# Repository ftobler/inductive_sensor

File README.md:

# inductive sensor with STM32

This is a open source inductive sensor using a STM32G030K8T6 MCU.

---

PCB has been made with Eagle, Software with STM32CubeIDE.

The sensor is capable of sub mm accuracy. There might be linearity errors.

The TX coil is driven with 125kHz. A new measurement can be made every 50ms. The speed is limited mainly due to lack of processing power and FPU. During one measurement, the TX coil is ON for 2.8ms. During the short ON time, data is gathered which is later processed. The amount which can be gathered is limited by RAM available.

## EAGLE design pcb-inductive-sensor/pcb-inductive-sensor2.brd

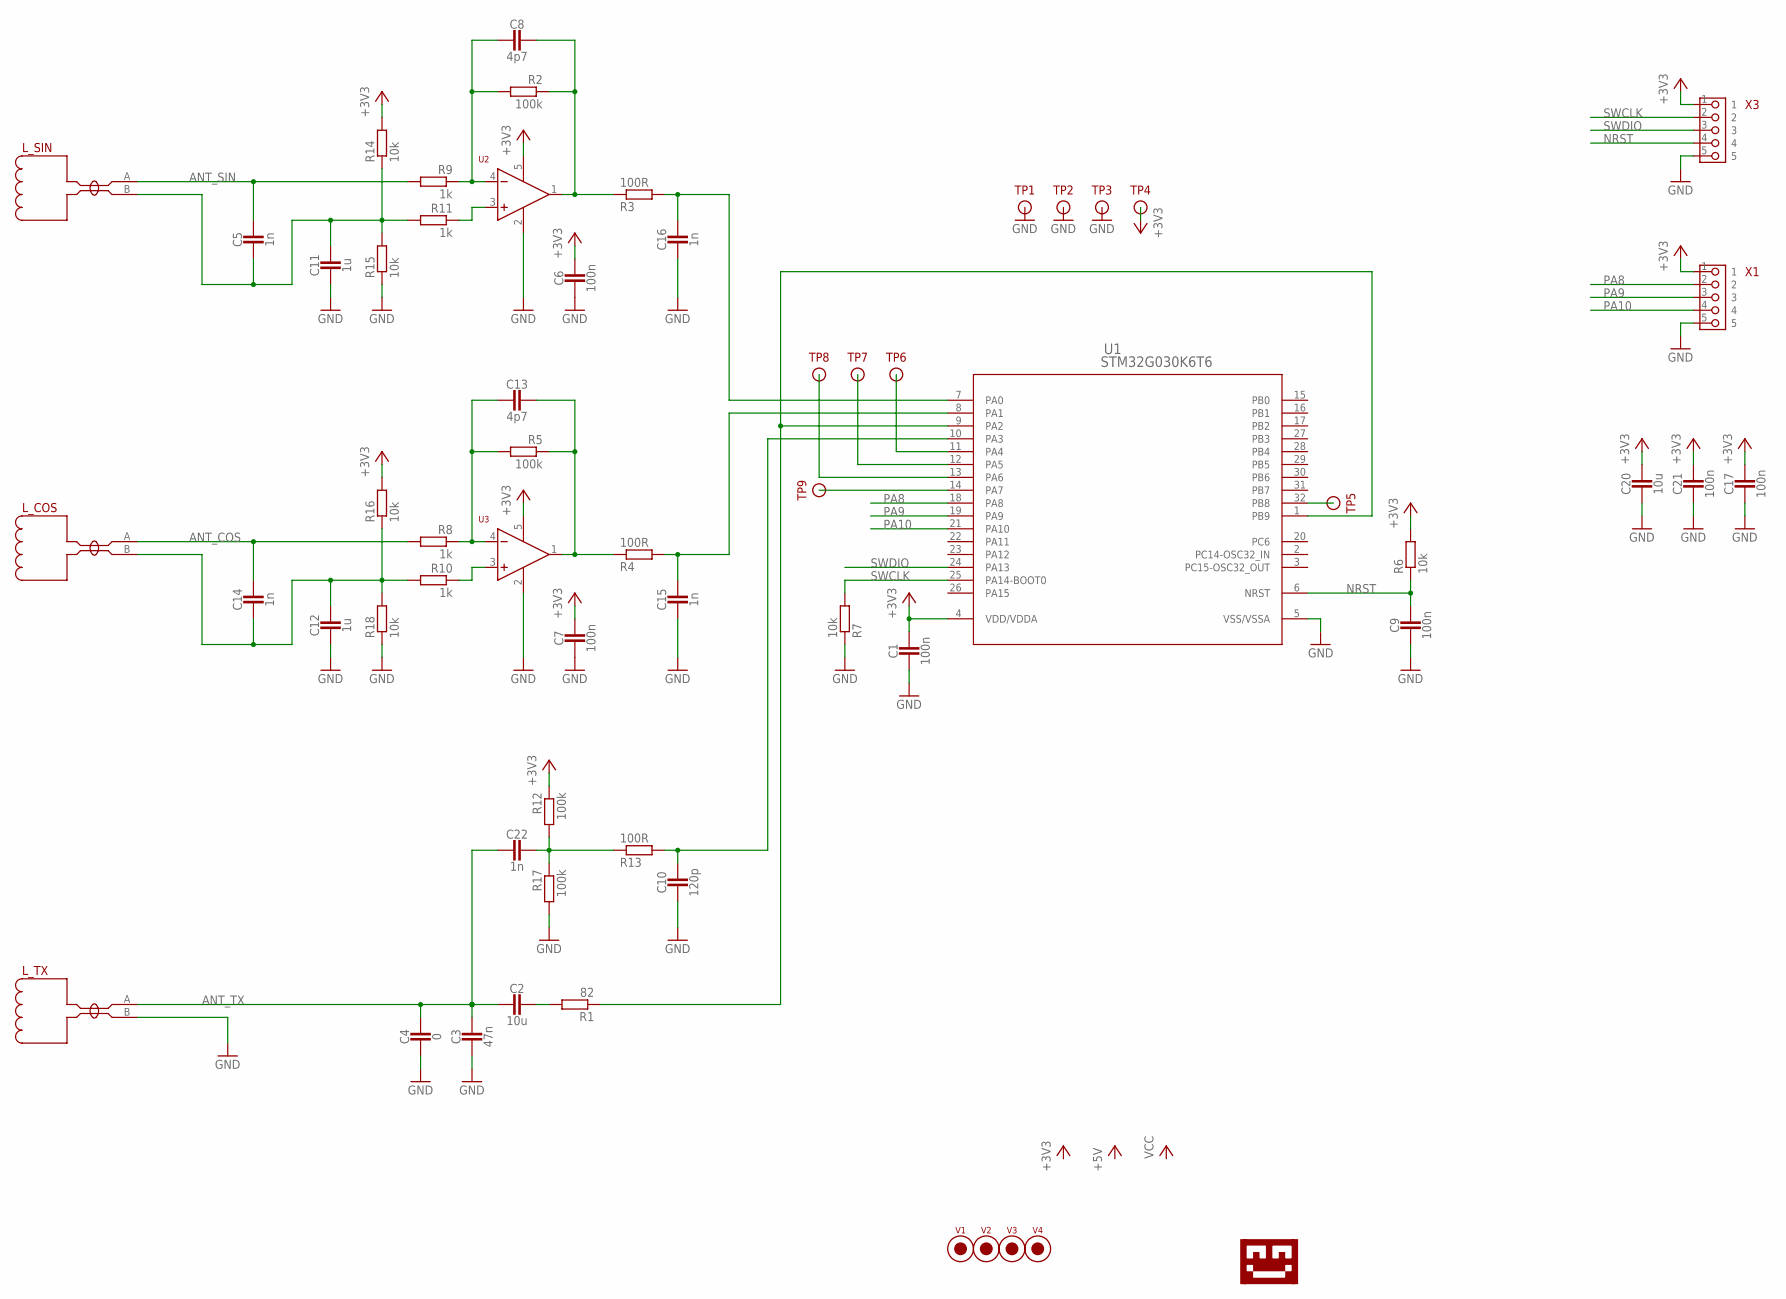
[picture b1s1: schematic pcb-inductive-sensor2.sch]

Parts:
C1, C6, C7, C9, C17, C21: 100n; 0603_CAP
C2, C20: 10u; 0805_CAP
C3: 47n; 0603_CAP
C4: 0; 0603_CAP
C5, C14, C15, C16, C22: 1n; 0603_CAP
C8, C13: 4p7; 0603_CAP
C10: 120p; 0603_CAP
C11, C12: 1u; 0603_CAP
L_COS: INDUCTION_SENSOR; INDUCTIVE_SENSOR_NET_TIE
L_SIN: INDUCTION_SENSOR; INDUCTIVE_SENSOR_NET_TIE
L_TX: INDUCTION_SENSOR; INDUCTIVE_SENSOR_NET_TIE
R1: 82; 0805_RES
R2, R5, R12, R17: 100k; 0603-RES
R3, R4, R13: 100R; 0603-RES
R6, R7, R14, R15, R16, R18: 10k; 0603-RES
R8, R9, R10, R11: 1k; 0603-RES
TP1, TP2, TP3, TP4, TP5, TP6, TP7, TP8, TP9: TESTPIN; PIN-SMD-1X1-TEST_1M5
U1: STM32G030K6T6; LQFP-32
U2, U3: OPAMP-TLV3541IDBVT; SOT-23-5
U$1: LOGO-TOBENG-1MM-FINISH; TOBENG-1MM-FINISH
V1, V2, V3, V4: FIDUCIAL2MM; FIDUCIAL_2MM
X1, X3: PIN_5X1HD; PIN_5X1_HD

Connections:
+3V3: C1.1, C6.1, C7.1, C17.1, C20.P$1 (1), C21.1, R6.2, R12.1, R14.2, R16.2, TP4.1, U1.4 (VDD/VDDA), U2.5 (VCC), U3.5 (VCC), X1.1, X3.1
ANT_COS: C14.1, L_COS.A, R8.2
ANT_SIN: C5.1, L_SIN.A, R9.2
ANT_TX: C2.P$2 (2), C3.1, C4.1, C22.2, L_TX.A
ANT_TX1: R1.1, U1.1 (PB9), U1.9 (PA2)
GND: C1.2, C3.2, C4.2, C6.2, C7.2, C9.2, C10.2, C11.2, C12.2, C15.2, C16.2, C17.2, C20.P$2 (2), C21.2, L_TX.B, R7.1, R15.1, R17.2, R18.1, TP1.1, TP2.1, TP3.1, U1.5 (VSS/VSSA), U2.2 (GND), U3.2 (GND), X1.5, X3.5
unnamed: C16.1, R3.2, U1.7 (PA0)
unnamed: C15.1, R4.2, U1.8 (PA1)
unnamed: C10.1, R13.2, U1.10 (PA3)
unnamed: TP6.1, U1.11 (PA4)
unnamed: TP7.1, U1.12 (PA5)
unnamed: TP8.1, U1.13 (PA6)
unnamed: TP9.1, U1.14 (PA7)
unnamed: C8.1, R2.1, R3.1, U2.1 (OUT)
unnamed: C8.2, R2.2, R9.1, U2.4 (-)
unnamed: TP5.1, U1.32 (PB8)
unnamed: C13.1, R4.1, R5.1, U3.1 (OUT)
unnamed: C13.2, R5.2, R8.1, U3.4 (-)
unnamed: C22.1, R12.2, R13.1, R17.1
unnamed: R11.1, U2.3 (+)
unnamed: R10.1, U3.3 (+)
unnamed: C2.P$1 (1), R1.2
unnamed: C12.1, C14.2, L_COS.B, R10.2, R16.1, R18.2
unnamed: C5.2, C11.1, L_SIN.B, R11.2, R14.1, R15.2
NRST: C9.1, R6.1, U1.6 (NRST), X3.4
PA8: U1.18 (PA8), X1.2
PA9: U1.19 (PA9), X1.3
PA10: U1.21 (PA10), X1.4
SWCLK: R7.2, U1.25 (PA14-BOOT0), X3.2
SWDIO: U1.24 (PA13), X3.3

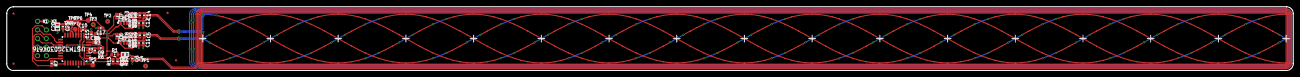
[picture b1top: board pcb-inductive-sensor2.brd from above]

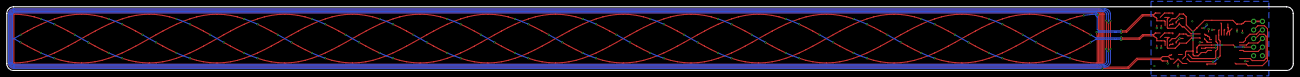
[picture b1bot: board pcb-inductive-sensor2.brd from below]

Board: 2 copper layers, 380.0 x 18.8 mm, 60 parts (2 on the bottom side), 30 nets.

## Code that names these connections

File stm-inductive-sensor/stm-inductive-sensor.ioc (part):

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Mcu.Name=STM32G030K(6-8)Tx
Mcu.Package=LQFP32
Mcu.UserName=STM32G030K8Tx
PA0.Mode=IN0
PA0.Signal=ADC1_IN0
PA1.Mode=IN1
PA1.Signal=ADC1_IN1
PA10.Signal=GPIO_Output
PA13.Mode=Serial_Wire
PA13.Signal=SYS_SWDIO
PA14-BOOT0.Mode=Serial_Wire
PA14-BOOT0.Signal=SYS_SWCLK
PA3.Mode=IN3
PA3.Signal=ADC1_IN3
PA8.Signal=S_TIM1_CH1
PA9.Mode=Asynchronous
PA9.Signal=USART1_TX
PB7.Mode=Asynchronous
PB7.Signal=USART1_RX
PB9.Signal=S_TIM17_CH1
RCC.HSE_VALUE=8000000
RCC.SYSCLKFreq_VALUE=64000000
RCC.SYSCLKSource=RCC_SYSCLKSOURCE_PLLCLK
board=custom

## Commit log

2023-12-27 stm32 project running prototype
2023-12-27 ignore eagle and stm cube
2023-12-27 deleted unused rtos
2023-12-27 measurement optimization and output
2023-12-28 comments
2023-12-28 higher output accuracy, more samples, less computations
2023-12-28 eagle pcb with improvement comments
2023-12-28 readme
2023-12-28 add another image
2024-01-24 calibration for 2nd pcb revision
2024-01-26 pcb version 2
2024-01-26 gerber data

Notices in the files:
parts and their libraries:
COPYRIGHT: Copyright (C) 2018 Accelerated Designs. All rights reserved
